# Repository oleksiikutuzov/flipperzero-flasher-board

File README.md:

# flipperzero-flasher-board

Since version 0.70.1 you can set RTS/DTR pins to pins 16/15 and use only one row of pins for this flasher board.

I made this simple board to flash my ESP32 projects. It uses the [ESPFlash](https://github.com/SuperHouse/ESPFlash) pinout. Flasher has a switch to toggle 3.3V from Flipper Zero if you need to power the device you are flashing from an external power source. Recommended PCB thickness is 1.0 - 1.2 mm.

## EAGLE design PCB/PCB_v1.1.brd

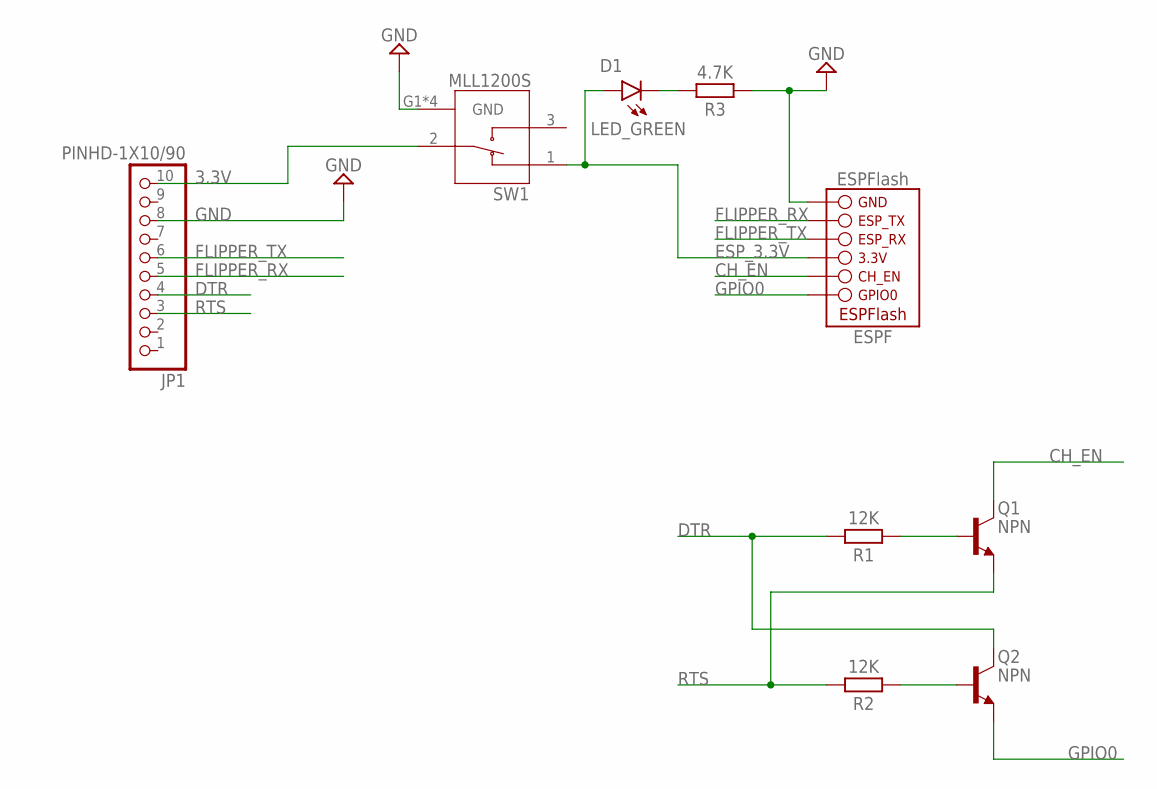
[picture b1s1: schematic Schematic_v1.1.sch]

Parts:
D1: LED_GREEN; LEDC1608X55N_FLAT-B
ESPF: ESPFLASH-1X6-2.54-PLAIN; 1X6-2.54-PLAIN
JP1: PINHD-1X10/90; 1X10/90
Q1, Q2: NPN; SOT95P237X112-3N
R1, R2: 12K; RESC1608X60
R3: 4.7K; RESC1608X60
SW1: MLL1200S; SW_MLL1200S

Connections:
3.3V: JP1.10, SW1.2
CH_EN: ESPF.5 (CH_EN), Q1.3 (C)
DTR: JP1.4, Q2.3 (C), R1.1
ESP_3.3V: D1.A, ESPF.4 (3.3V), SW1.1
FLIPPER_RX: ESPF.2 (ESP_TX), JP1.5
FLIPPER_TX: ESPF.3 (ESP_RX), JP1.6
GND: ESPF.1 (GND), JP1.8, R3.2, SW1.G1 (GND), SW1.G2 (GND), SW1.G3 (GND), SW1.G4 (GND)
GPIO0: ESPF.6 (GPIO0), Q2.2 (E)
unnamed: D1.C, R3.1
unnamed: Q1.1 (B), R1.2
unnamed: Q2.1 (B), R2.2
RTS: JP1.3, Q1.2 (E), R2.1

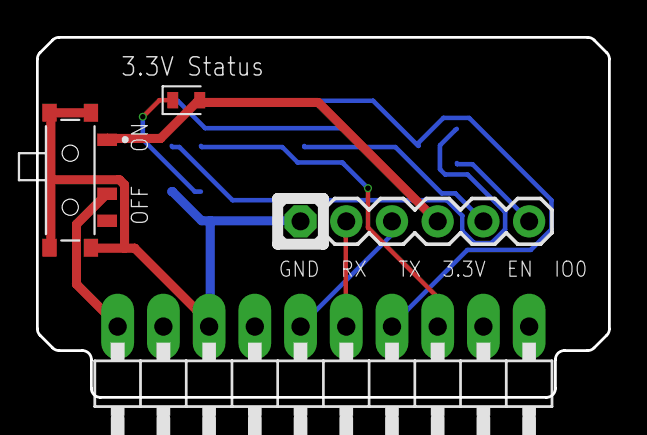
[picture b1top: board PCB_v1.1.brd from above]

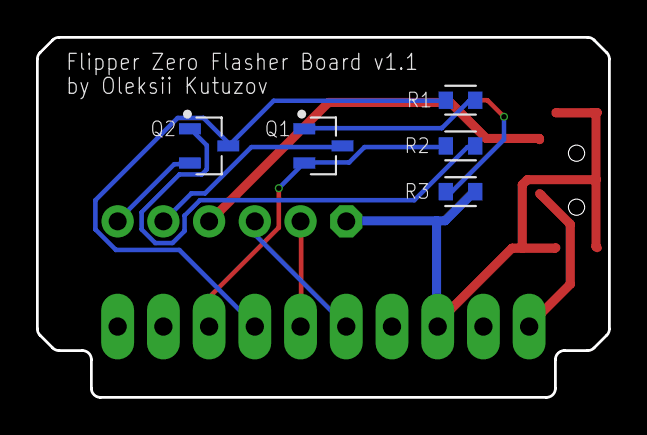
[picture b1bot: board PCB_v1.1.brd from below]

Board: 2 copper layers, 31.8 x 20.0 mm, 9 parts (5 on the bottom side), 12 nets.

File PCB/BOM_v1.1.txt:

Partlist exported from /var/folders/tq/b2m_bkf11ld61j4hqq2g93cr0000gn/T/Neutron/ElectronFileOutput/14894/sch-362ab598-894d-49ed-90d1-658ffdb2f589/Schematic v7.sch at 27.10.22 18:26

Part Value                   Device                   Package             Description                                              
D1   LED_GREEN               CHIP-FLAT-B_0603-0.55MM  LEDC1608X55N_FLAT-B                                                          
ESPF ESPFLASH-1X6-2.54-PLAIN ESPFLASH-1X6-2.54-PLAIN  1X6-2.54-PLAIN      ESPFlash                                                 
JP1  PINHD-1X10/90           PINHD-1X10/90            1X10/90             PIN HEADER                                               
Q1   NPN                     NPN_SOT23-BEC            SOT95P237X112-3N    NPN - Generic                                            
Q2   NPN                     NPN_SOT23-BEC            SOT95P237X112-3N    NPN - Generic                                            
R1   12K                     R_CHIP-0603(1608-METRIC) RESC1608X60         Resistor Fixed - Generic                                 
R2   12K                     R_CHIP-0603(1608-METRIC) RESC1608X60         Resistor Fixed - Generic                                 
R3   4.7K                    R_CHIP-0603(1608-METRIC) RESC1608X60         Resistor Fixed - Generic                                 
SW1  MLL1200S                MLL1200S                 SW_MLL1200S         Switch Slide SPDT Side Slide 0.3A 4VDC Gull Wing SMD Box 
                                                                          https://a.aliexpress.com/_EyNVWSJ

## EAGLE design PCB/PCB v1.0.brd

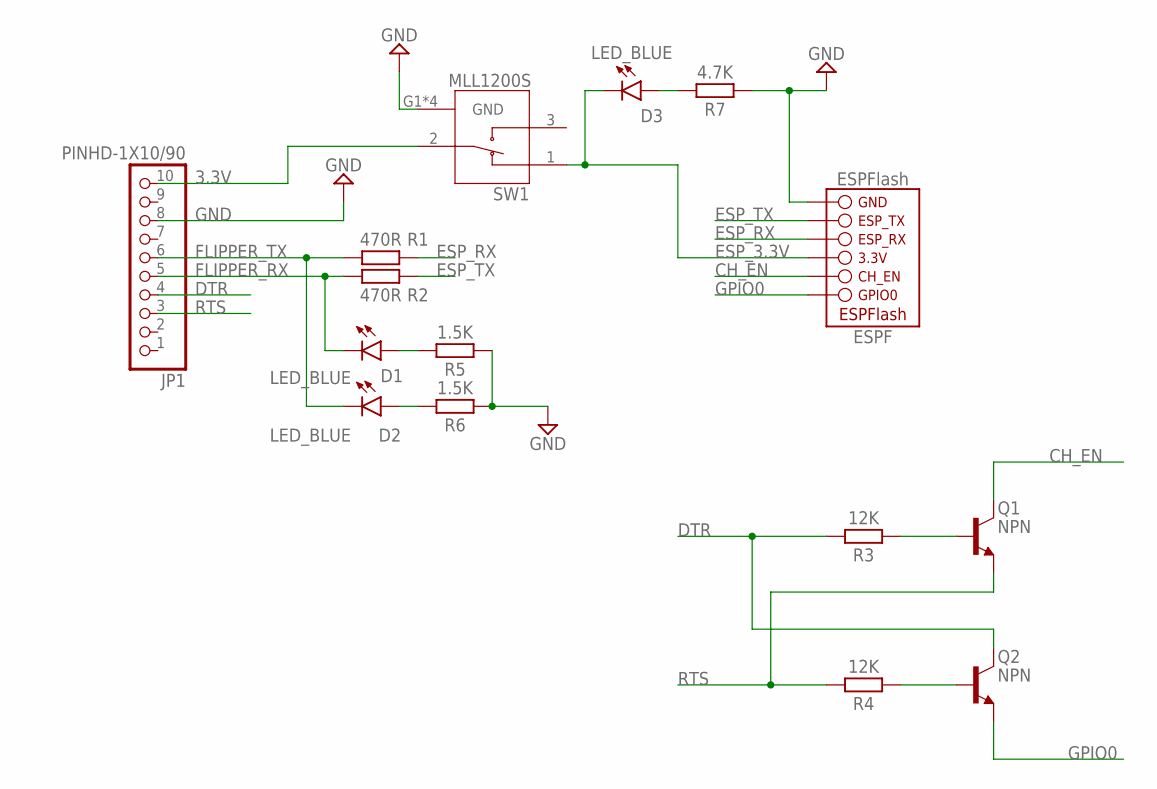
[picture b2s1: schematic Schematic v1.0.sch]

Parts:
D1, D2, D3: LED_BLUE; LEDC1608X55N_FLAT-B
ESPF: ESPFLASH-1X6-2.54-PLAIN; 1X6-2.54-PLAIN
JP1: PINHD-1X10/90; 1X10/90
Q1, Q2: NPN; SOT95P237X112-3N
R1, R2: 470R; RESC1608X60
R3, R4: 12K; RESC1608X60
R5, R6: 1.5K; RESC1608X60
R7: 4.7K; RESC1608X60
SW1: MLL1200S; SW_MLL1200S

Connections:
3.3V: JP1.10, SW1.2
CH_EN: ESPF.5 (CH_EN), Q1.3 (C)
DTR: JP1.4, Q2.3 (C), R3.1
ESP_3.3V: D3.C, ESPF.4 (3.3V), SW1.1
ESP_RX: ESPF.3 (ESP_RX), R1.2
ESP_TX: ESPF.2 (ESP_TX), R2.2
FLIPPER_RX: D1.C, JP1.5, R2.1
FLIPPER_TX: D2.C, JP1.6, R1.1
GND: ESPF.1 (GND), JP1.8, R5.2, R6.2, R7.2, SW1.G1 (GND), SW1.G2 (GND), SW1.G3 (GND), SW1.G4 (GND)
GPIO0: ESPF.6 (GPIO0), Q2.2 (E)
unnamed: D1.A, R5.1
unnamed: Q1.1 (B), R3.2
unnamed: D2.A, R6.1
unnamed: Q2.1 (B), R4.2
unnamed: D3.A, R7.1
RTS: JP1.3, Q1.2 (E), R4.1

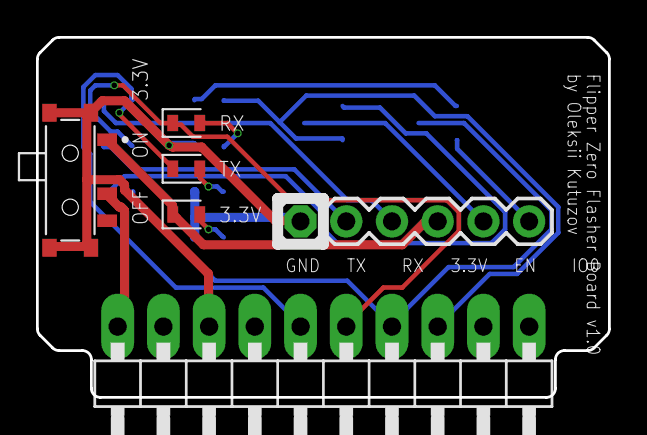
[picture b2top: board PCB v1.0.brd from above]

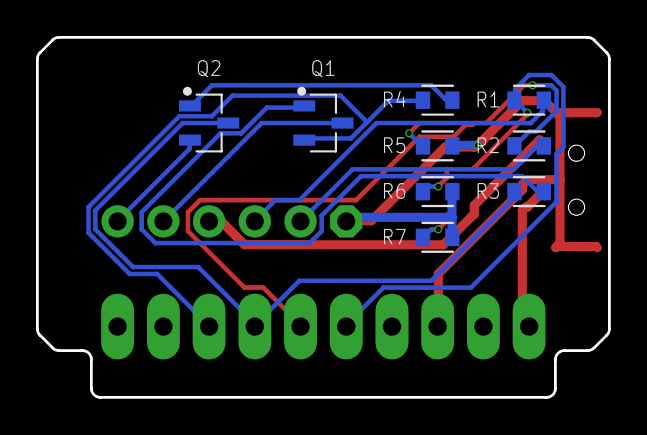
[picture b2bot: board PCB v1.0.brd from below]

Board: 2 copper layers, 31.8 x 20.0 mm, 15 parts (9 on the bottom side), 16 nets.

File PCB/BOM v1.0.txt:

Partlist exported from /var/folders/33/ch3jvwxj20q4dc1rxcvrc1bm0000gn/T/Neutron/ElectronFileOutput/53817/sch-77be259d-dd1d-4473-aec8-f9fe45a27142/Schematic v6.sch at 13.10.22 23:43

Part Value                   Device                   Package             Description
D1   LED_BLUE                CHIP-FLAT-B_0603-0.55MM  LEDC1608X55N_FLAT-B
D2   LED_BLUE                CHIP-FLAT-B_0603-0.55MM  LEDC1608X55N_FLAT-B
D3   LED_BLUE                CHIP-FLAT-B_0603-0.55MM  LEDC1608X55N_FLAT-B
ESPF ESPFLASH-1X6-2.54-PLAIN ESPFLASH-1X6-2.54-PLAIN  1X6-2.54-PLAIN      ESPFlash
JP1  PINHD-1X10/90           PINHD-1X10/90            1X10/90             PIN HEADER
Q1   NPN                     NPN_SOT23-BEC            SOT95P237X112-3N    NPN - Generic
Q2   NPN                     NPN_SOT23-BEC            SOT95P237X112-3N    NPN - Generic
R1   470R                    R_CHIP-0603(1608-METRIC) RESC1608X60         Resistor Fixed - Generic
R2   470R                    R_CHIP-0603(1608-METRIC) RESC1608X60         Resistor Fixed - Generic
R3   12K                     R_CHIP-0603(1608-METRIC) RESC1608X60         Resistor Fixed - Generic
R4   12K                     R_CHIP-0603(1608-METRIC) RESC1608X60         Resistor Fixed - Generic
R5   1.5K                    R_CHIP-0603(1608-METRIC) RESC1608X60         Resistor Fixed - Generic
R6   1.5K                    R_CHIP-0603(1608-METRIC) RESC1608X60         Resistor Fixed - Generic
R7   4.7K                    R_CHIP-0603(1608-METRIC) RESC1608X60         Resistor Fixed - Generic
SW1  MLL1200S                MLL1200S                 SW_MLL1200S         Switch Slide SPDT Side Slide 0.3A 4VDC Gull Wing SMD Box
                                                                          https://a.aliexpress.com/_EyNVWSJ

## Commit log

2022-10-13 Add files
2022-10-13 Add image with flipper
2022-10-14 Crop pictures
2022-10-27 Fix schematic
2022-10-27 Add firmware version to readme
2022-10-27 Add photos
2022-10-27 Add suggested PCB thickness
